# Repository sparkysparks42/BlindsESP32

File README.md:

# ESP32 Smart Blinds (Arduino Cloud)

A DIY motorised blind controller. An ESP32 drives two DC gear motors through a TB6612FNG motor driver and is controlled from the **Arduino Cloud (IoT Cloud) dashboard**, so you can open and close the blinds from a phone or browser (and from voice assistants, via Arduino Cloud's Alexa/Google integrations, since the main property is a `CloudLight`).

The blinds are moved by pulling the bead (ball) chain with a drive wheel on each motor. Each motor is stopped when a magnet (reed) switch shows that its drive wheel has **stalled** at the end of the blind's travel. A maximum run time acts only as a safety timeout.

## How it works

### Cloud variables (Thing properties)

| Variable | Type | Access | Purpose |
|---|---|---|---|
| `blinds` | `CloudLight` | read/write | Main control. **On = open (up), Off = closed (down).** Triggers the full automatic move. |
| `blindSwitch` | `bool` | read/write | Manual mode only: selects which motor the Up/Down buttons drive (see below). |
| `up` | `bool` | read/write | Manual jog: hold to run the selected motor up, release to stop. |
| `down` | `bool` | read/write | Manual jog: hold to run the selected motor down, release to stop. |
| `uptime` | `int` | read only | Seconds since boot, updated every ~10 s. Handy as a "is it alive" indicator. |

Suggested dashboard widgets: a Switch/Light for `blinds`, a Switch for `blindSwitch`, two Push Buttons for `up`/`down`, and a Value/Chart for `uptime`.

### Automatic open/close

When `blinds` changes, the sketch moves the **two motors one after the other** (motor 1 first, then motor 2), at full speed for up to `BLIND_UP_SECONDS` / `BLIND_DOWN_SECONDS` (10 s in the current sketch), stopping early on a stall (see below). They deliberately run one at a time, never together (see [Why only one motor at a time](#why-only-one-motor-at-a-time)). Details:

- The sketch tracks a software state (`opened` / `closed` / `unknown`). Asking for the state it already thinks it is in does nothing.
- Commands received while the blinds are moving are ignored.
- The first change message received after boot is ignored (the cloud re-syncs stored values on connect, and this stops the blinds moving every time the board restarts). **The initial state is "unknown", so the first real command after power-up will move the blinds** regardless of where they physically are.
- The state is not stored in flash, so it is lost on reboot. If the blinds and the software state disagree, use the manual buttons to put the blinds where you want them.

### Stall detection (magnet sensors)

Each motor has a normally-closed magnet reed sensor (`MAGR` on GPIO14 for motor 1, `MAGL` on GPIO32 for motor 2) wired from input to ground with a 10 kΩ pull-up to 3.3 V. The previous GPIO13/GPIO27 sensor-power wiring is removed. While a motor runs in an automatic move, the sketch reads its sensor every 10 ms loop. If the sensor value has not changed for more than 30 reads, and the motor has been running for at least 30 loops, the motor is declared stalled ("Motor 1 Stall" / "Motor 2 Stall" in the serial log) and the sketch moves on to the next motor, or finishes. This is how the blinds stop at the top and bottom without limit switches. The fixed run time is only an upper bound if no stall is seen.

- Stall detection is used for automatic moves only, not the manual `up` / `down` buttons.
- The sketch notes that the check may be susceptible to switch bounce if the magnet rests close to the sensor.
- The sketch prints several serial lines every 10 ms while moving, which makes the serial log very noisy.

### Manual mode

`blindSwitch` chooses the motor, then `up` / `down` run it while held: `blindSwitch` = Off drives motor 2, On drives motor 1. This is for trimming each side individually (e.g. if the two sides drift out of level) and is ignored while an automatic move is in progress.

### Why only one motor at a time

Do not change the code to run both motors together without upgrading the hardware. Each motor is rated 0.92 A, so two need about 1.84 A at rated load (more at start-up or stall), which is above the 12 V / 1.7 A supply. The TB6612FNG breakout has no heatsink and cannot dissipate the heat of driving both. A driver was destroyed when this was tried. If you want simultaneous motion, use a larger supply, motors with lower current draw, and a driver with proper heatsinking (or a separate driver per motor).

### Tuning

Edit these `#define`s in `BlindsESP32_apr16a.ino`:

- `BLIND_UP_SECONDS`, `BLIND_DOWN_SECONDS` – maximum run time for each motor; set a little longer than a full travel so stall detection normally ends the move.
- `BLIND_UP` / `BLIND_DOWN` – motor direction (+1 / -1); the motor driver always runs at full speed.
- `offsetA`, `offsetB` – set to `-1` to flip a motor's direction if it spins the wrong way.

Mechanical note from the original build: drive wheel diameter is 30.6 mm (≈96 mm circumference), and the bead chain has 16 balls per wheel revolution.

## CAD

The motor mount is modelled in Tinkercad: [Blinds motor mount](https://www.tinkercad.com/things/eyJbsuSWBMM-blinds-motor-mount?sharecode=2IoUn7R2jkvfn2GjVcyLNe40DJcVV0ZCj15O-5fbk3I).

The 2-layer electronics carrier and wired schematic are in the [KiCad project](PCB/BlindsController.kicad_pro), [PCB](PCB/BlindsController.kicad_pcb), and [schematic](PCB/BlindsController.kicad_sch). The board is routed with GND pours on both sides. The corrected [Gerber package](PCB/manufacturing/BlindsController-Gerbers-2026-11-10-mask-fix.zip), fabrication notes, and final checks are under `PCB/manufacturing/`.

## Repository layout

| File | What it is |
|---|---|
| `BlindsESP32_apr16a.ino` | Main sketch (the name comes from Arduino Cloud, which does not allow renaming the main file): pin mapping, motion logic, cloud callbacks. |
| `thingProperties.h` | Auto-generated by Arduino Cloud: declares the cloud variables and connects them. Contains a placeholder device ID. |
| `arduino_secrets.h.example` | Template for WiFi / device credentials. Copy to `arduino_secrets.h` (git-ignored). |
| `motor_driver.h/.cpp` | Small driver for one TB6612FNG channel: direction pins, an on/off enable pin, standby. Full speed only (no PWM). |
| `PCB/` | KiCad sources, project-local symbol and footprint libraries, and manufacturing outputs. |
| `sketch.json` | Arduino Cloud sketch metadata (board FQBN, secret names). Values are empty. |

## Hardware

| Part | Notes |
|---|---|
| ESP32 dev board | Built for "ESP32 Dev Module" (`esp32:esp32:esp32`), 4 MB flash. Any ESP32 supported by Arduino Cloud should work. |
| TB6612FNG dual motor driver | SparkFun TB6612FNG breakout board (ROB-14450). |
| 2 × DC gear motors | [12 V DC gearmotor, 100 RPM, eccentric D-shaft](https://www.amazon.com/dp/B0721T1PXQ) – one on each side of the blind, driving a bead-chain wheel. 1:47.5 reduction, rated 3.6 kg·cm and 0.92 A, 6×14 mm D-shaft, 37 mm gearbox, M3 mounting holes. Stall current not published. |
| 2 × bead-chain drive wheels | 30.6 mm diameter, 16 balls per revolution. |
| Motor power supply | 12 V DC wall adapter, 1.7 A (feeds TB6612 `VM`). |
| 5 V buck converter module | The listed 4-pin module converts 4.5-24 V to 5 V. PCB pad order: EN (left open), IN+, GND, VO. Confirm the module is configured for fixed 5 V before use. [Amazon listing](https://www.amazon.com/dp/B08JZ5FVLC). |
| 2 × magnetic reed switches | Normally-closed door/window-alarm style reed switch, one per motor, read on GPIO32 / GPIO14 (4-pack, [Amazon](https://www.amazon.com/dp/B07VQ1DY6T)). Closed when the magnet is near, open when it moves away. |
| 2 × 10 kΩ resistors | Through-hole pull-ups from each reed input to 3.3 V. |
| Status LED (+ resistor) | Optional, on GPIO19; blinks every loop iteration as a liveness indicator. |

### Wiring

| ESP32 GPIO | TB6612FNG pin | Function |
|---|---|---|
| 16 | AIN1 | Motor 1 direction |
| 17 | AIN2 | Motor 1 direction |
| 5 | PWMA | Motor 1 speed |
| 4 | BIN1 | Motor 2 direction |
| 0 | BIN2 | Motor 2 direction |
| 2 | PWMB | Motor 2 speed |
| 18 | STBY | Standby / enable |
| 19 | – | Status LED (to GND via resistor) |
| 14 | magnet sensor, motor 1 (`MAGR`) | Digital input, 10 kΩ pull-up to 3.3 V; normally-closed reed returns to GND |
| 32 | magnet sensor, motor 2 (`MAGL`) | Digital input, 10 kΩ pull-up to 3.3 V; normally-closed reed returns to GND |
| 3V3 | VCC | TB6612 logic supply directly from ESP32 3.3 V |
| GND | GND | Common ground with motor supply |
| – | VM | Motor supply (+) |
| – | A01/A02, B01/B02 | Motor 1 and motor 2 |

> GPIO0 and GPIO2 are ESP32 strapping pins and connect to TB6612 inputs; check that the breakout does not bias them into an invalid boot state. Reed switches connect each sensor input to GND when closed. Through-hole 10 kΩ resistors pull both inputs up to 3.3 V. The left sensor uses GPIO32 instead of GPIO12 so its pull-up cannot affect GPIO12 flash-voltage strapping. GPIO13/GPIO27 sensor power outputs are no longer used.

Wiring diagram (derived from the pin definitions in the sketch):

```
                      12 V DC wall adapter
                         (+)         (-)
                          |           |
                          |           +-----------------------+
                          |                                   |
   +----------------------+-----+      +----------------------+---+
   |  SparkFun TB6612FNG        |      |        ESP32 Dev Module  |
   |  breakout (ROB-14450)      |      |                          |
   |                            |      |                          |
   |  VM   <--------------------+      |                          |
   |  VCC  <------------------------------ 3V3 (direct PCB connection) |
   |  GND  <------------------------+---- GND  (common ground)    |
   |                            |      |                          |
   |  AIN1 <------------------------------ GPIO16                 |
   |  AIN2 <------------------------------ GPIO17                 |
   |  PWMA <------------------------------ GPIO5                  |
   |  BIN1 <------------------------------ GPIO4                  |
   |  BIN2 <------------------------------ GPIO0                  |
   |  PWMB <------------------------------ GPIO2                  |
   |  STBY <------------------------------ GPIO18                 |
   |                            |      |                          |
   |  A01 / A02 ---> Motor 1    |      |  GPIO19 --[R]--|>|-- GND |
   |  B01 / B02 ---> Motor 2    |      |           (status LED)   |
   +----------------------------+      +--------------------------+
```

Notes:

- **Common ground:** the wall adapter's negative, the TB6612 `GND` and the ESP32 `GND` must all be connected together.
- **5 V supply:** The PCB buck module takes the adapter input and feeds its VO output to the ESP32 `5V`/`VIN` pin. EN is intentionally left unconnected. Verify the module is configured for 5 V and measure its output before connecting the ESP32.

- **Motor polarity:** if a motor runs the wrong way, swap its two wires or flip `offsetA` / `offsetB` in the sketch.
- Consider a bulk capacitor (e.g. 100 µF or more) across `VM` and `GND` near the driver to absorb motor switching spikes.

## Setup and deployment

You need an [Arduino Cloud](https://cloud.arduino.cc) account (the free tier is enough for one Thing).

### How Arduino Cloud fits together

Arduino Cloud has four pieces that you set up in order. The menu names below are from the current web interface and may change.

| Piece | What it is | In this project |
|---|---|---|
| **Device** | The physical board registered with the Cloud. Gives you a Device ID and a Secret Key. | One ESP32, created as a *third-party device*. |
| **Thing** | The device plus its cloud variables and WiFi settings. Generates `thingProperties.h` and the sketch skeleton. | One Thing with the five variables listed above. |
| **Sketch** | The code, edited, compiled and uploaded in the Cloud's web editor. Belongs to the Thing. | `BlindsESP32_apr16a.ino` plus `motor_driver.*`. |
| **Dashboard** | The web/phone control panel with widgets linked to the variables. | Switch, buttons and a value for the blinds. |

**Board selection:** this project is built for a generic ESP32. When you create the device, and again whenever the editor asks you to choose a board for compiling and uploading, pick **ESP32 Dev Module** (`esp32:esp32:esp32`). The original build used these board settings (from `sketch.json`); if the editor or your IDE exposes them, use the same values:

| Setting | Value |
|---|---|
| CPU frequency | 240 MHz |
| Flash size | 4 MB |
| Flash mode / frequency | QIO / 80 MHz |
| Partition scheme | Default |
| PSRAM | Disabled |
| Upload speed | 921600 |
| Core debug level | None |

### 1. Create the device

1. In Arduino Cloud go to **Devices → Add → Third party device → ESP32 → ESP32 Dev Module**.
2. Connect the ESP32 to your computer with a data-capable USB cable when prompted and select its serial port. This needs the **Arduino Cloud Agent** (the browser will offer to install it) and a Chrome-based browser.
3. Name the device (for example "Blinds"). When it finishes, **save the Device ID and Secret Key** – the secret key is shown only once and goes into the Secret tab later.

### 2. Create the Thing

1. **Things → Create**. Under *Associated Device* select the device from step 1. Under *Network* choose WiFi and enter your 2.4 GHz WiFi name and password (the ESP32 does not support 5 GHz).
2. Add the variables from the table above with exactly these names and types:
   - `blinds` – type **Smart Home → Light (`CloudLight`)**, Read & Write, *Update on change*
   - `blindSwitch`, `down`, `up` – Boolean, Read & Write, *Update on change*
   - `uptime` – Integer, Read only, *Update on change*
3. Open the **Sketch** tab. Arduino Cloud generates `thingProperties.h` (with your own device ID) and the `.ino` skeleton.

### 3. Add the code

Easiest path (Arduino Cloud web editor):

1. In the Sketch tab, replace the `.ino` contents with `BlindsESP32_apr16a.ino` from this repo (keep the `#include "arduino_secrets.h"` first line).
2. Add `motor_driver.h` and `motor_driver.cpp` as new files in the sketch (*▾ → New tab / Upload*).
3. Leave the Cloud-generated `thingProperties.h` as is – **do not** paste this repo's placeholder over it.
4. Fill in the **Secret** tab: `SECRET_SSID`, `SECRET_OPTIONAL_PASS`, `SECRET_DEVICE_KEY`.
5. At the top of the editor, select your device or choose board **ESP32 Dev Module** and the serial port of the connected ESP32.
6. Click **Verify** (compile), then **Upload**. If the upload stalls at "Connecting...", hold the ESP32's **BOOT** button until it starts.
7. Open the editor's **Serial Monitor** at 115200 baud to watch the log.

Alternative (local Arduino IDE / arduino-cli):

1. Install the ESP32 board package (`esp32` by Espressif) and the **ArduinoIoTCloud** and **Arduino_ConnectionHandler** libraries (they pull in their dependencies).
2. Put the files in a folder named `BlindsESP32_apr16a` (the folder name must match the `.ino`, so the cloned repo folder must be renamed).
3. `cp arduino_secrets.h.example arduino_secrets.h` and fill it in.
4. Replace the placeholder device ID in `thingProperties.h` with your Device ID (or copy the generated `thingProperties.h` from the Cloud).
5. Select board *ESP32 Dev Module*, 240 MHz, 4 MB flash, default partition scheme, and upload.

### 4. Build the dashboard

**Dashboards → Create → Build dashboard**, then *Add* widgets and link each to a variable of your Thing:

| Widget | Linked variable | Notes |
|---|---|---|
| Switch (or Light) | `blinds` | On = open, Off = closed. |
| Switch | `blindSwitch` | Chooses which motor the manual buttons drive. |
| Push button | `up` | Hold to run the selected motor up. A push button sends on while pressed and off when released, which is what the sketch expects. |
| Push button | `down` | Hold to run the selected motor down. |
| Value or Chart | `uptime` | Shows the board is alive. |

Optionally enable the Alexa or Google Home integration from the Cloud to control `blinds` by voice. Open the dashboard on your phone with the Arduino Cloud app.

### 5. Commission and calibrate

1. Power up with the blinds in a known position and open the Serial Monitor at 115200 baud. You should see `***Booted***`, then cloud connection messages and `Uptime=` every ~10 s.
2. Use the manual `up` / `down` buttons (with `blindSwitch` selecting the motor) to confirm each motor turns the right way. If not, flip its `offsetA` / `offsetB`.
3. Check the sensors: with the serial monitor open, run a motor and confirm the `Motor ... ticks` count resets as the wheel turns. If it never resets, check sensor power, wiring and magnet position.
4. Time a full travel of the blinds and set `BLIND_UP_SECONDS` / `BLIND_DOWN_SECONDS` a little above it. Re-upload.
5. Test `blinds` on/off. Keep a hand near the power supply for the first runs – stall detection is the only thing that stops the blinds at the ends before the timeout, so if a sensor fails the motor will keep pulling until the timeout.

## Known limitations

- End of travel is found by stall detection (a safety timeout backs it up), but there is no absolute position measurement. The software open/closed state is lost on reboot.
- Stall detection relies on the magnet sensors and fixed thresholds (30 loops); there is no electrical current protection.
- Fixed full-speed moves; motors run sequentially by design (see below).
- The manual `up` / `down` buttons do not set the "moving" flag, so changing `blinds` while a manual button is held (or changing `blindSwitch` mid-jog) can run both motors at once. See [Why only one motor at a time](#why-only-one-motor-at-a-time); avoid doing this.
- `uptime` increments by 10 per ~10 s but drifts slightly (it is counted in loop iterations).

## Security note

WiFi credentials and the Arduino Cloud device secret key belong only in `arduino_secrets.h` (git-ignored) or the Cloud's Secret tab. If you ever committed real values in a fork, regenerate the device's secret key in Arduino Cloud.

## License and credits

- The motor driver (`motor_driver.*`) is original code; it was written after starting from SparkFun's MIT-licensed [TB6612FNG library](https://github.com/sparkfun/SparkFun_TB6612FNG_Arduino_Library), which is no longer included.
- This project is released under the [MIT License](LICENSE).

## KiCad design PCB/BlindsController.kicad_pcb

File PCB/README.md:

# Blinds controller KiCad design

**Current fabrication package:** [corrected solder-mask ZIP](manufacturing/BlindsController-Gerbers-2026-11-10-mask-fix.zip). This supersedes the original ordered package; replace the order files with this complete export.

The reviewed KiCad PCB is routed on two copper layers. The 12 V motor supply trace is 1.2 mm wide for the specified 1 A load, assuming 1 oz copper. GND traces are 1.2 mm wide; +5 V and +3.3 V supply traces are 0.6 mm wide; motor outputs are 0.6 mm. Signal traces are 0.25 mm. Vias are 0.8 mm with 0.4 mm drills.

## Changes for review

- Preserved the component placements and used the PCB's concise values consistently in both views.
- Corrected the SparkFun TB6612FNG v11 breakout mapping using its Eagle board: 20.32 mm square module, 15.24 mm header separation, 2.54 mm pitch. Pad identifiers now use SparkFun header/pin identifiers JP1.1 through JP1.8 and JP2.1 through JP2.8.
- Top view, VM at upper left: left row top to bottom = VM, VCC, GND, AO1, AO2, BO2, BO1, GND; right row = PWMA, AIN2, AIN1, STBY, BIN1, BIN2, PWMB, GND.
- Connected all three driver ground pins in the netlist. VCC is 3.3 V; VM is 12 V. Buck EN remains intentionally open.
- Repaired the schematic input-capacitor wire that joined 12 V to GND and repaired sensor wire endpoint gaps.
- Corrected MAGL to physical ESP32 header pad 7 (GPIO32); pad 13 is GPIO12 and is unused. Firmware remains GPIO32 for MAGL and GPIO14 for MAGR.
- Added four non-plated 2.7 mm mounting holes for M2.5 standoffs. Centers: (116,68.5), (183,68.5), (116,129.5), (183,129.5) mm. Expanded each board edge by 4 mm to preserve placements and clear the hardware. Outline is now 74 x 68 mm.
- Restored stable schematic UUID paths on every footprint and added matching project-local symbol/footprint libraries. Open BlindsController.kicad_pro; normal Update PCB from Schematic uses these links.

## Source files and checks

The .kicad_sch and .kicad_pcb files are the maintained sources. The Blinds.pretty directory, Blinds.kicad_sym, fp-lib-table and sym-lib-table are part of the project and must travel with it. Historical generators are archived and must not overwrite the edited design.

ERC: zero violations. Schematic/PCB parity: zero issues. Current PCB DRC reports zero violations and zero unconnected items. Schematic/PCB parity reports zero issues. See erc.txt and parity.txt for the current reports.

Local working backups and historical generators are ignored by Git. The ordered fabrication release and source snapshots are retained under manufacturing/2026-11-10/.

References:
- https://github.com/sparkfun/Motor_Driver-Dual_TB6612FNG/blob/master/Hardware/SparkFun_Motor_Driver-TB6612FNG_v11.brd
- https://docs.espressif.com/projects/esp-dev-kits/en/latest/esp32/esp32-devkitc/user_guide.html

## Routing cleanup

Replaced the grid staircases with straight clearance-checked runs and simple bends. Track segments decreased from 1,093 to 196, with 31 vias. The 12 V motor supply remains 1.2 mm wide. Footprint placements and net assignments are unchanged. Current checks: zero DRC violations, zero unconnected items, zero schematic/PCB parity issues. Prior routing drafts are retained locally in ignored backups.

## Ground planes

Added filled GND zones on F.Cu and B.Cu with 0.25 mm clearance and disconnected islands removed. The ESP32 antenna end is excluded from both pours. Input connector J3 GND and all three driver J2 GND pads use solid connections to the planes; other pads use thermal reliefs where feasible. GND traces are 1.2 mm wide, matching the 12 V rail. The input ground joins the filled plane through a 1.2 mm wide bottom-layer entry. Both planes are connected by through-hole GND pads. No component placements were changed. Final DRC and schematic/PCB parity: zero violations and zero unconnected items.

## Fabrication export

The original ordered ZIP, now superseded by the mask correction, is `manufacturing/BlindsController-Gerbers-2026-11-10.zip`. Fabrication notes, source snapshots, export hashes and final check reports are in `manufacturing/2026-11-10/`. This export was made after refilling the ground zones and passing DRC, ERC, connectivity and schematic/PCB parity checks. Board specifications: 74 x 68 mm, two copper layers, 1.6 mm FR4, 1 oz copper per side.

## Version control

Commit the KiCad project, schematic, board, Blinds.pretty/, Blinds.kicad_sym, and both library tables together. Release Gerbers, drill files, the ordering ZIP, check reports, source snapshots, and any BOM CSV outputs belong in Git. Local session files, locks, working backups, temporary candidates, and historical generators are ignored. No BOM CSV had been generated at the time of this initial CAD commit.

## Solder-mask correction

The former custom component pads omitted mask layers. All 84 plated component pads now have explicit openings on both mask layers, verified in the exported Gerbers (88 flashes per side including the four mounting holes). Standard KiCad footprints now replace the resistor, test-point and LED placeholders; the other standard component footprints reference their official library IDs. Only ESP32 and TB6612 modules remain in Blinds.pretty. LED symbol numbering was adjusted to standard pin 1 cathode / pin 2 anode while preserving physical polarity and wiring. DRC, ERC and schematic/PCB parity pass. Use the mask-fix release and its current source snapshot for manufacturing.

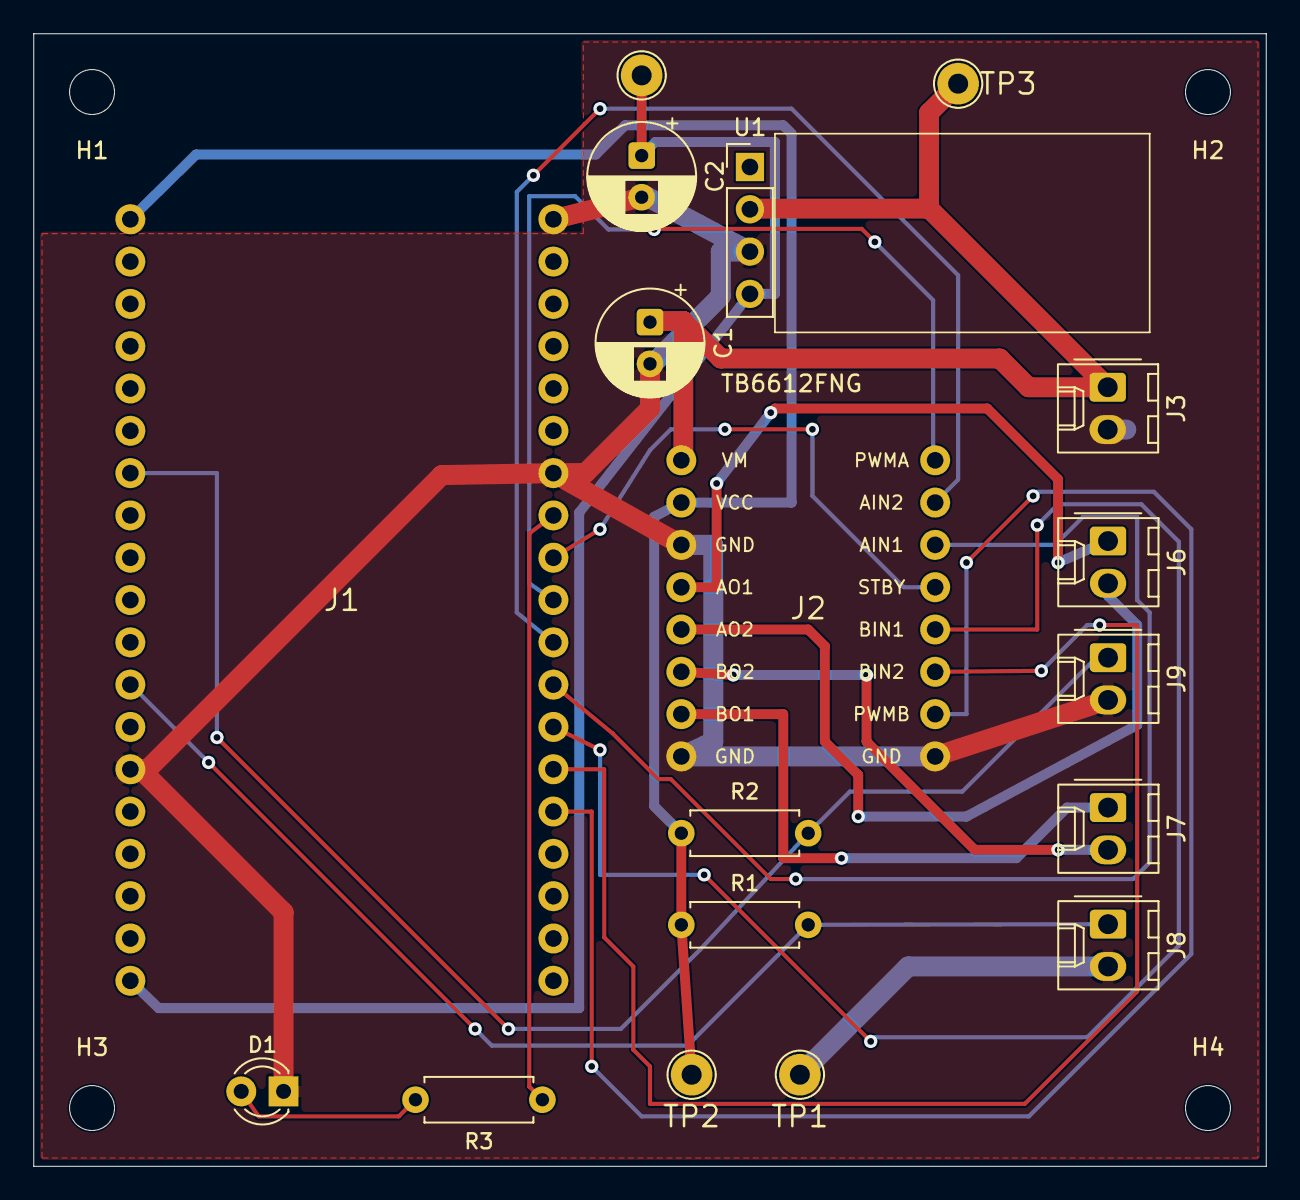
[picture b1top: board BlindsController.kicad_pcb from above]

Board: 2 copper layers, 74.0 x 68.0 mm, 22 parts (0 on the bottom side), 19 nets.

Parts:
C1: 100uF 25V; CP_Radial_D6.3mm_P2.50mm
C2: 100uF 10V; CP_Radial_D6.3mm_P2.50mm
D1: STATLED; LED_D3.0mm
H1, H2, H3, H4: M2.5; MountingHole_2.7mm_M2.5
J1: ESP32 DEVKITC 38P; Carrier_J1
J2: TB6612FNG; Carrier_J2
J3: 12V IN; Molex_KK-254_AE-6410-02A_1x02_P2.54mm_Vertical
J6: MTR1; Molex_KK-254_AE-6410-02A_1x02_P2.54mm_Vertical
J7: MTR2; Molex_KK-254_AE-6410-02A_1x02_P2.54mm_Vertical
J8: MAG2; Molex_KK-254_AE-6410-02A_1x02_P2.54mm_Vertical
J9: MAG1; Molex_KK-254_AE-6410-02A_1x02_P2.54mm_Vertical
R1, R2: 10K; R_Axial_DIN0207_L6.3mm_D2.5mm_P7.62mm_Horizontal
R3: 330R; R_Axial_DIN0207_L6.3mm_D2.5mm_P7.62mm_Horizontal
TP1: GND; TestPoint_THTPad_D2.5mm_Drill1.2mm
TP2: 3V3; TestPoint_THTPad_D2.5mm_Drill1.2mm
TP3: 12V; TestPoint_THTPad_D2.5mm_Drill1.2mm
TP4: 5V; TestPoint_THTPad_D2.5mm_Drill1.2mm
U1: 5V BUCK MODULE; PinHeader_1x04_P2.54mm_Vertical

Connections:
+3V3: J1.1, J2.JP1.7, R1.1, R2.1, TP2.1
+5V: C2.1, J1.19, TP4.1, U1.4
+12V: C1.1, J2.JP1.8, J3.1, TP3.1, U1.2
AIN1: J1.31, J2.JP2.3
AIN2: J1.30, J2.JP2.2
BIN1: J1.32, J2.JP2.5
BIN2: J1.33, J2.JP2.6
GND: C1.2, C2.2, D1.1, J1.14, J1.20, J1.26, J2.JP1.1, J2.JP1.6, J2.JP2.8, J3.2, J8.2, J9.2, TP1.1, U1.3
LED_A: D1.2, R3.2
LED_GPIO: J1.27, R3.1
M1_A: J2.JP1.5, J6.1
M1_B: J2.JP1.4, J6.2
M2_A: J2.JP1.2, J7.1
M2_B: J2.JP1.3, J7.2
MAGL: J1.7, J9.1, R2.2
MAGR: J1.12, J8.1, R1.2
PWMA: J1.29, J2.JP2.1
PWMB: J1.34, J2.JP2.7
STBY: J1.28, J2.JP2.4

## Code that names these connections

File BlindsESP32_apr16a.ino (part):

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#include "motor_driver.h"

// TB6612FNG pin assignments (the PWMx pins are used as plain on/off enables)
#define AIN1 16
#define AIN2 17
#define PWMA 5
#define BIN1 4
#define BIN2 0
#define PWMB 2
#define STBY 18

// Magnet (reed) sensor inputs, one per motor. Used to detect when a motor has
// stopped turning (stall / end of travel).
#define MAGL 32   // sensor for motor 2 (left), moved off GPIO12 for pull-up/strap safety
#define MAGR 14   // sensor for motor 1 (right)

// motor direction (the driver always runs at full speed)
#define BLIND_UP 1
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  motor1 = Motor(AIN1, AIN2, PWMA, offsetA, STBY);
  motor2 = Motor(BIN1, BIN2, PWMB, offsetB, STBY);

  pinMode(MAGR,INPUT);
  pinMode(MAGL,INPUT);

  // Defined in thingProperties.h
  initProperties();
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

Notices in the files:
BlindsESP32_apr16a.ino:
Copyright (c) 2026 Mike Costa
Released under the MIT License (see LICENSE).
